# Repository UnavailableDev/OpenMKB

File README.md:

# OpenMKB
Modular keyboard (wip)

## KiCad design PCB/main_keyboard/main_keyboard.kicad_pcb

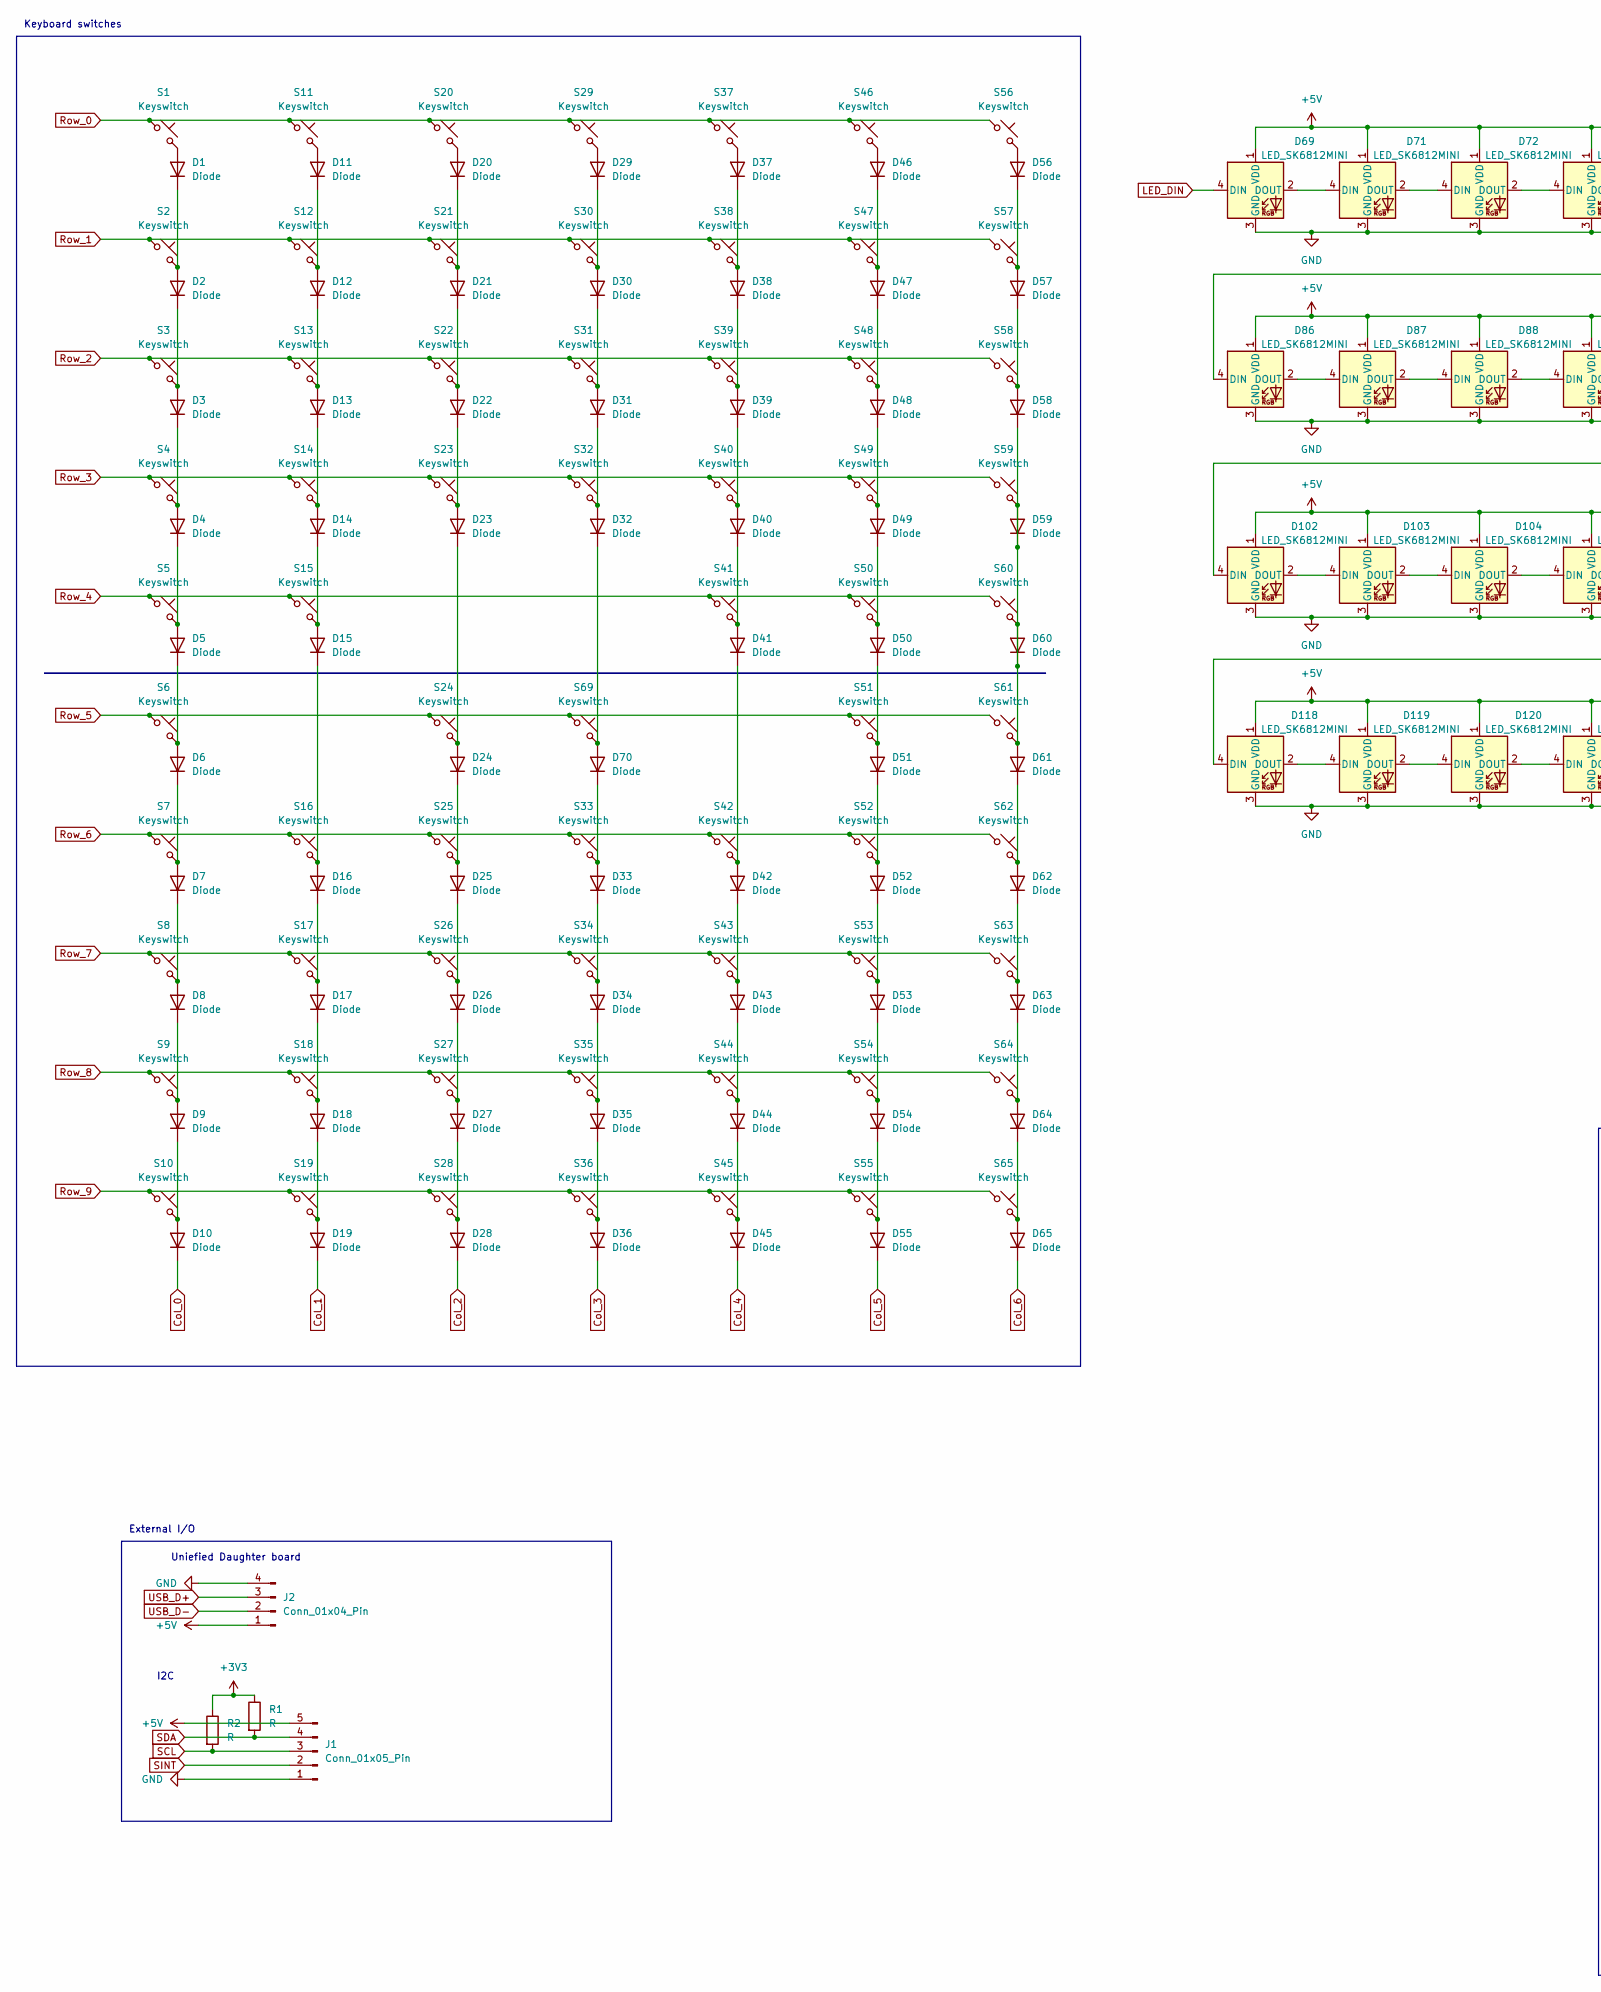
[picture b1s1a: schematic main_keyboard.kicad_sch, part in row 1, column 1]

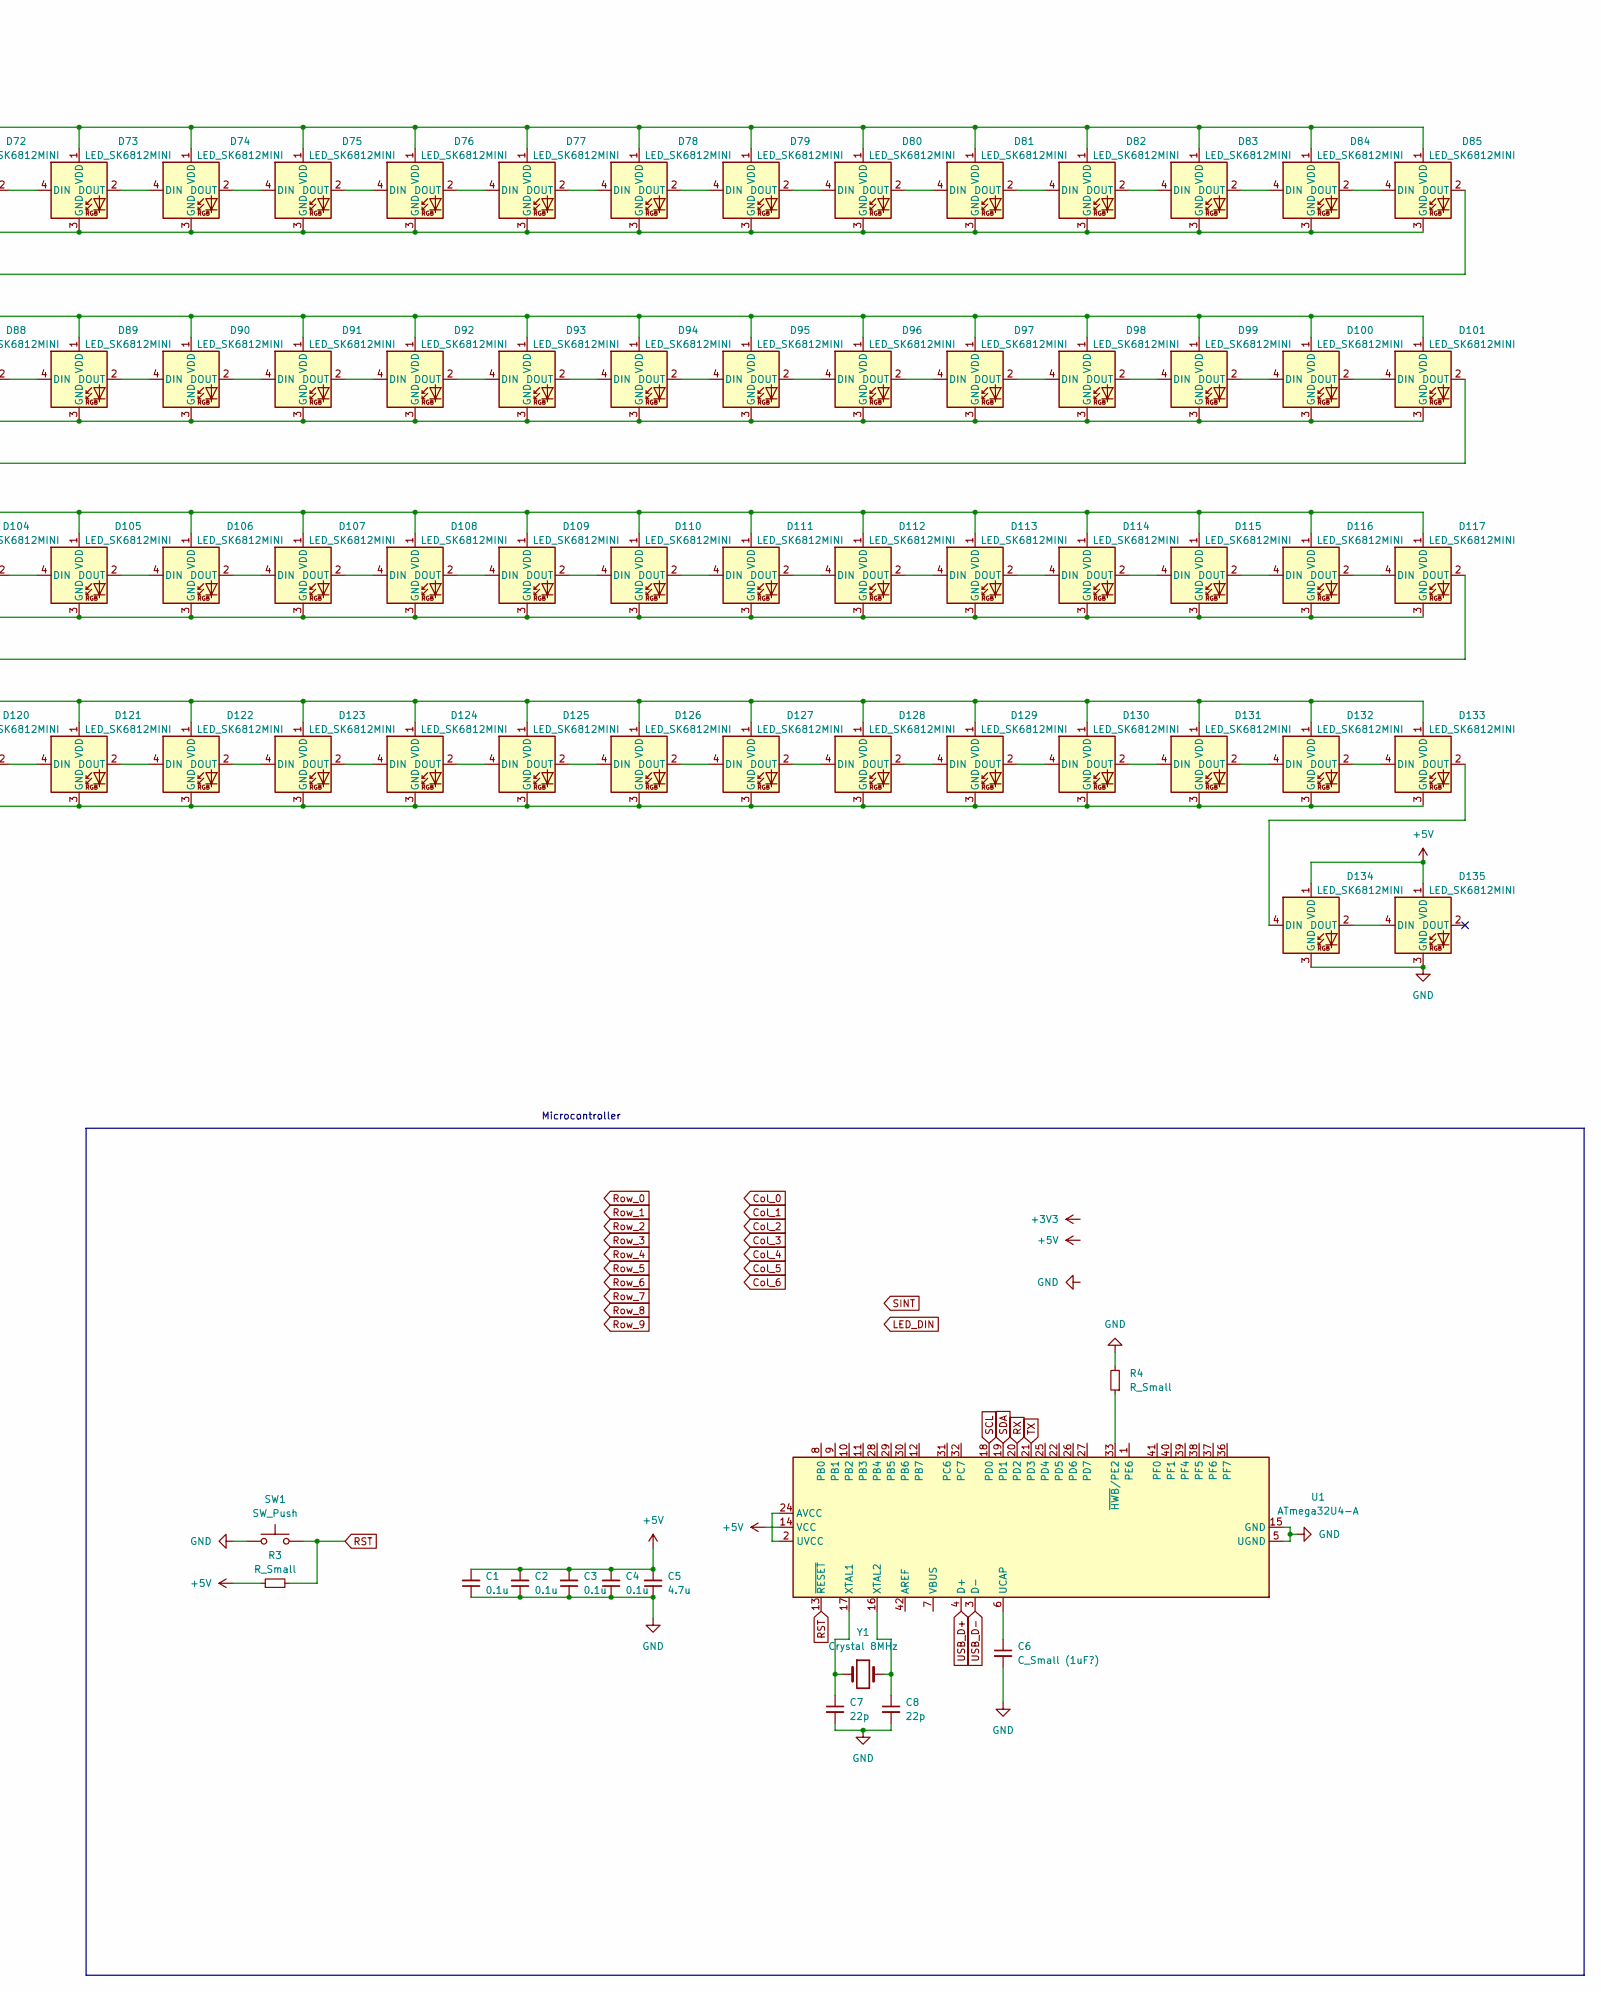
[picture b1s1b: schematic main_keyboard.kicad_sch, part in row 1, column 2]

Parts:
C1, C2, C3, C4: 0.1u; C_01005_0402Metric_Pad0.57x0.30mm_HandSolder
C5: 4.7u; C_0201_0603Metric_Pad0.64x0.40mm_HandSolder
C6: C_Small (1uF?)
C7, C8: 22p; C_01005_0402Metric_Pad0.57x0.30mm_HandSolder
D1, D2, D3, D4, D5, D6, D7, D8, D9, D10, D11, D12, D13, D14, D15, D16, D17, D18, D19, D20, D21, D22, D23, D24, D25, D26, D27, D28, D29, D30, D31, D32, D33, D34, D35, D36, D37, D38, D39, D40, D41, D42, D43, D44, D45, D46, D47, D48, D49, D50, D51, D52, D53, D54, D55, D56, D57, D58, D59, D60, D61, D62, D63, D64, D65, D70: Diode; Diode_SOD-123
D69, D71, D72, D73, D74, D75, D76, D77, D78, D79, D80, D81, D82, D83, D84, D85, D86, D87, D88, D89, D90, D91, D92, D93, D94, D95, D96, D97, D98, D99, D100, D101, D102, D103, D104, D105, D106, D107, D108, D109, D110, D111, D112, D113, D114, D115, D116, D117, D118, D119, D120, D121, D122, D123, D124, D125, D126, D127, D128, D129, D130, D131, D132, D133, D134, D135: LED_SK6812MINI
J1: Conn_01x05_Pin; FanPinHeader_1x03_P2.54mm_Vertical
J2: Conn_01x04_Pin
R1, R2: R
R3, R4: R_Small
S1, S7, S8, S9, S10, S11, S12, S13, S14, S16, S17, S18, S19, S20, S21, S22, S23, S25, S26, S27, S28, S29, S30, S31, S32, S33, S34, S35, S36, S37, S38, S39, S40, S42, S43, S44, S45, S46, S47, S48, S49, S51, S53, S54, S55, S56, S57, S59, S60, S61, S62, S63: Keyswitch; Hotswap_MX_Plated_1.00u
S2, S64: Keyswitch; Hotswap_MX_Plated_1.50u
S3, S24: Keyswitch; Hotswap_MX_Plated_1.75u
S4, S15, S58, S69: Keyswitch; Hotswap_MX_Plated_2.25u
S5, S6, S41, S50, S52: Keyswitch; Hotswap_MX_Plated_1.25u
S65: Keyswitch; Hotswap_MX_Plated_2.00u
SW1: SW_Push
U1: ATmega32U4-A; TQFP-44_10x10mm_P0.8mm
Y1: Crystal 8MHz

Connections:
+5V: C1.2, C2.2, C3.2, C4.2, C5.2, D69.1 (VDD), D71.1 (VDD), D72.1 (VDD), D73.1 (VDD), D74.1 (VDD), D75.1 (VDD), D76.1 (VDD), D77.1 (VDD), D78.1 (VDD), D79.1 (VDD), D80.1 (VDD), D81.1 (VDD), D82.1 (VDD), D83.1 (VDD), D84.1 (VDD), D85.1 (VDD), D86.1 (VDD), D87.1 (VDD), D88.1 (VDD), D89.1 (VDD), D90.1 (VDD), D91.1 (VDD), D92.1 (VDD), D93.1 (VDD), D94.1 (VDD), D95.1 (VDD), D96.1 (VDD), D97.1 (VDD), D98.1 (VDD), D99.1 (VDD), D100.1 (VDD), D101.1 (VDD), D102.1 (VDD), D103.1 (VDD), D104.1 (VDD), D105.1 (VDD), D106.1 (VDD), D107.1 (VDD), D108.1 (VDD), D109.1 (VDD), D110.1 (VDD), D111.1 (VDD), D112.1 (VDD), D113.1 (VDD), D114.1 (VDD), D115.1 (VDD), D116.1 (VDD), D117.1 (VDD), D118.1 (VDD), D119.1 (VDD), D120.1 (VDD), D121.1 (VDD), D122.1 (VDD), D123.1 (VDD), D124.1 (VDD), D125.1 (VDD), D126.1 (VDD), D127.1 (VDD), D128.1 (VDD), D129.1 (VDD), D130.1 (VDD), D131.1 (VDD), D132.1 (VDD), D133.1 (VDD), D134.1 (VDD), D135.1 (VDD), J1.5, J2.1, R3.1, U1.14 (VCC), U1.34 (VCC)
Col_0: D10.1 (K)
Col_1: D19.1 (K)
Col_2: D28.1 (K)
Col_3: D36.1 (K)
Col_4: D45.1 (K)
Col_5: D55.1 (K)
Col_6: D65.1 (K)
GND: C1.1, C2.1, C3.1, C4.1, C5.1, C6.2, C7.2, C8.2, D69.3 (GND), D71.3 (GND), D72.3 (GND), D73.3 (GND), D74.3 (GND), D75.3 (GND), D76.3 (GND), D77.3 (GND), D78.3 (GND), D79.3 (GND), D80.3 (GND), D81.3 (GND), D82.3 (GND), D83.3 (GND), D84.3 (GND), D85.3 (GND), D86.3 (GND), D87.3 (GND), D88.3 (GND), D89.3 (GND), D90.3 (GND), D91.3 (GND), D92.3 (GND), D93.3 (GND), D94.3 (GND), D95.3 (GND), D96.3 (GND), D97.3 (GND), D98.3 (GND), D99.3 (GND), D100.3 (GND), D101.3 (GND), D102.3 (GND), D103.3 (GND), D104.3 (GND), D105.3 (GND), D106.3 (GND), D107.3 (GND), D108.3 (GND), D109.3 (GND), D110.3 (GND), D111.3 (GND), D112.3 (GND), D113.3 (GND), D114.3 (GND), D115.3 (GND), D116.3 (GND), D117.3 (GND), D118.3 (GND), D119.3 (GND), D120.3 (GND), D121.3 (GND), D122.3 (GND), D123.3 (GND), D124.3 (GND), D125.3 (GND), D126.3 (GND), D127.3 (GND), D128.3 (GND), D129.3 (GND), D130.3 (GND), D131.3 (GND), D132.3 (GND), D133.3 (GND), D134.3 (GND), D135.3 (GND), J1.1, J2.4, R4.2, SW1.1, U1.5 (UGND), U1.15 (GND), U1.23 (GND), U1.35 (GND), U1.43 (GND)
LED_DIN: D69.4 (DIN)
unnamed: D1.2 (A), S1.2
unnamed: D1.1 (K), D2.2 (A), S2.2
unnamed: D2.1 (K), D3.2 (A), S3.2
unnamed: D3.1 (K), D4.2 (A), S4.2
unnamed: D4.1 (K), D5.2 (A), S5.2
unnamed: D5.1 (K), D6.2 (A), S6.2
unnamed: D6.1 (K), D7.2 (A), S7.2
unnamed: D7.1 (K), D8.2 (A), S8.2
unnamed: D8.1 (K), D9.2 (A), S9.2
unnamed: D9.1 (K), D10.2 (A), S10.2
unnamed: D11.2 (A), S11.2
unnamed: D11.1 (K), D12.2 (A), S12.2
unnamed: D12.1 (K), D13.2 (A), S13.2
unnamed: D13.1 (K), D14.2 (A), S14.2
unnamed: D14.1 (K), D15.2 (A), S15.2
unnamed: D15.1 (K), D16.2 (A), S16.2
unnamed: D16.1 (K), D17.2 (A), S17.2
unnamed: D17.1 (K), D18.2 (A), S18.2
unnamed: D18.1 (K), D19.2 (A), S19.2
unnamed: D20.2 (A), S20.2
unnamed: D20.1 (K), D21.2 (A), S21.2
unnamed: D21.1 (K), D22.2 (A), S22.2
unnamed: D22.1 (K), D23.2 (A), S23.2
unnamed: D23.1 (K), D24.2 (A), S24.2
unnamed: D24.1 (K), D25.2 (A), S25.2
unnamed: D25.1 (K), D26.2 (A), S26.2
unnamed: D26.1 (K), D27.2 (A), S27.2
unnamed: D27.1 (K), D28.2 (A), S28.2
unnamed: D29.2 (A), S29.2
unnamed: D29.1 (K), D30.2 (A), S30.2
unnamed: D30.1 (K), D31.2 (A), S31.2
unnamed: D31.1 (K), D32.2 (A), S32.2
unnamed: D32.1 (K), D70.2 (A), S69.2
unnamed: D33.2 (A), D70.1 (K), S33.2
unnamed: D33.1 (K), D34.2 (A), S34.2
unnamed: D34.1 (K), D35.2 (A), S35.2
unnamed: D35.1 (K), D36.2 (A), S36.2
unnamed: D37.2 (A), S37.2
unnamed: D37.1 (K), D38.2 (A), S38.2
unnamed: D38.1 (K), D39.2 (A), S39.2
unnamed: D39.1 (K), D40.2 (A), S40.2
unnamed: D40.1 (K), D41.2 (A), S41.2
unnamed: D41.1 (K), D42.2 (A), S42.2
unnamed: D42.1 (K), D43.2 (A), S43.2
unnamed: D43.1 (K), D44.2 (A), S44.2
unnamed: D44.1 (K), D45.2 (A), S45.2
unnamed: D46.2 (A), S46.2
unnamed: D46.1 (K), D47.2 (A), S47.2
unnamed: D47.1 (K), D48.2 (A), S48.2
unnamed: D48.1 (K), D49.2 (A), S49.2
unnamed: D49.1 (K), D50.2 (A), S50.2
unnamed: D50.1 (K), D51.2 (A), S51.2
unnamed: D51.1 (K), D52.2 (A), S52.2
unnamed: D52.1 (K), D53.2 (A), S53.2
unnamed: D53.1 (K), D54.2 (A), S54.2
unnamed: D54.1 (K), D55.2 (A), S55.2
unnamed: D56.2 (A), S56.2
unnamed: D56.1 (K), D57.2 (A), S57.2
unnamed: D57.1 (K), D58.2 (A), S58.2
unnamed: D58.1 (K), D59.1 (K), D59.2 (A), D60.1 (K), D60.2 (A), D61.2 (A), S59.2, S60.2, S61.2
unnamed: D61.1 (K), D62.2 (A), S62.2
unnamed: D62.1 (K), D63.2 (A), S63.2
unnamed: D63.1 (K), D64.2 (A), S64.2
unnamed: D64.1 (K), D65.2 (A), S65.2
unnamed: D69.2 (DOUT), D71.4 (DIN)
unnamed: D71.2 (DOUT), D72.4 (DIN)
unnamed: D72.2 (DOUT), D73.4 (DIN)
unnamed: D73.2 (DOUT), D74.4 (DIN)
unnamed: D74.2 (DOUT), D75.4 (DIN)
unnamed: D75.2 (DOUT), D76.4 (DIN)
unnamed: D76.2 (DOUT), D77.4 (DIN)
unnamed: D77.2 (DOUT), D78.4 (DIN)
unnamed: D78.2 (DOUT), D79.4 (DIN)
unnamed: D79.2 (DOUT), D80.4 (DIN)
unnamed: D80.2 (DOUT), D81.4 (DIN)
unnamed: D81.2 (DOUT), D82.4 (DIN)
unnamed: D82.2 (DOUT), D83.4 (DIN)
unnamed: D83.2 (DOUT), D84.4 (DIN)
unnamed: D84.2 (DOUT), D85.4 (DIN)
unnamed: D85.2 (DOUT), D86.4 (DIN)
unnamed: D86.2 (DOUT), D87.4 (DIN)
unnamed: D87.2 (DOUT), D88.4 (DIN)
unnamed: D88.2 (DOUT), D89.4 (DIN)
unnamed: D89.2 (DOUT), D90.4 (DIN)
unnamed: D90.2 (DOUT), D91.4 (DIN)
unnamed: D91.2 (DOUT), D92.4 (DIN)
unnamed: D92.2 (DOUT), D93.4 (DIN)
unnamed: D93.2 (DOUT), D94.4 (DIN)
unnamed: D94.2 (DOUT), D95.4 (DIN)
unnamed: D95.2 (DOUT), D96.4 (DIN)
unnamed: D96.2 (DOUT), D97.4 (DIN)
unnamed: D97.2 (DOUT), D98.4 (DIN)
unnamed: D98.2 (DOUT), D99.4 (DIN)
unnamed: D99.2 (DOUT), D100.4 (DIN)
unnamed: D100.2 (DOUT), D101.4 (DIN)
unnamed: D101.2 (DOUT), D102.4 (DIN)
unnamed: D102.2 (DOUT), D103.4 (DIN)
unnamed: D103.2 (DOUT), D104.4 (DIN)
unnamed: D104.2 (DOUT), D105.4 (DIN)
unnamed: D105.2 (DOUT), D106.4 (DIN)
unnamed: D106.2 (DOUT), D107.4 (DIN)
unnamed: D107.2 (DOUT), D108.4 (DIN)
unnamed: D108.2 (DOUT), D109.4 (DIN)
unnamed: D109.2 (DOUT), D110.4 (DIN)
unnamed: D110.2 (DOUT), D111.4 (DIN)
unnamed: D111.2 (DOUT), D112.4 (DIN)
unnamed: D112.2 (DOUT), D113.4 (DIN)
unnamed: D113.2 (DOUT), D114.4 (DIN)
unnamed: D114.2 (DOUT), D115.4 (DIN)
unnamed: D115.2 (DOUT), D116.4 (DIN)
unnamed: D116.2 (DOUT), D117.4 (DIN)
unnamed: D117.2 (DOUT), D118.4 (DIN)
unnamed: D118.2 (DOUT), D119.4 (DIN)
unnamed: D119.2 (DOUT), D120.4 (DIN)
unnamed: D120.2 (DOUT), D121.4 (DIN)
unnamed: D121.2 (DOUT), D122.4 (DIN)
unnamed: D122.2 (DOUT), D123.4 (DIN)
unnamed: D123.2 (DOUT), D124.4 (DIN)
unnamed: D124.2 (DOUT), D125.4 (DIN)
unnamed: D125.2 (DOUT), D126.4 (DIN)
unnamed: D126.2 (DOUT), D127.4 (DIN)
unnamed: D127.2 (DOUT), D128.4 (DIN)
unnamed: D128.2 (DOUT), D129.4 (DIN)
unnamed: D129.2 (DOUT), D130.4 (DIN)
unnamed: D130.2 (DOUT), D131.4 (DIN)
unnamed: D131.2 (DOUT), D132.4 (DIN)
unnamed: D132.2 (DOUT), D133.4 (DIN)
unnamed: D133.2 (DOUT), D134.4 (DIN)
unnamed: D134.2 (DOUT), D135.4 (DIN)
unnamed: R1.1, R2.1
unnamed: C6.1, U1.6 (UCAP)
unnamed: U1.2 (UVCC), U1.24 (AVCC), U1.44 (AVCC)
unnamed: C7.1, U1.17 (XTAL1), Y1.1
unnamed: C8.1, U1.16 (XTAL2), Y1.2
unnamed: R4.1, U1.33 (~HWB/PE2)
RST: R3.2, SW1.2, U1.13 (~RESET)
RX: U1.20 (PD2)
Row_0: S1.1, S11.1, S20.1, S29.1, S37.1, S46.1, S56.1
Row_1: S2.1, S12.1, S21.1, S30.1, S38.1, S47.1, S57.1
Row_2: S3.1, S13.1, S22.1, S31.1, S39.1, S48.1, S58.1
Row_3: S4.1, S14.1, S23.1, S32.1, S40.1, S49.1, S59.1
Row_4: S5.1, S15.1, S41.1, S50.1, S60.1
Row_5: S6.1, S24.1, S51.1, S61.1, S69.1
Row_6: S7.1, S16.1, S25.1, S33.1, S42.1, S52.1, S62.1
Row_7: S8.1, S17.1, S26.1, S34.1, S43.1, S53.1, S63.1
Row_8: S9.1, S18.1, S27.1, S35.1, S44.1, S54.1, S64.1
Row_9: S10.1, S19.1, S28.1, S36.1, S45.1, S55.1, S65.1
SCL: J1.3, R2.2, U1.18 (PD0)
SDA: J1.4, R1.2, U1.19 (PD1)
SINT: J1.2
TX: U1.21 (PD3)
USB_D+: J2.3, U1.4 (D+)
USB_D-: J2.2, U1.3 (D-)

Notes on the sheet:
External I/O
I2C
Keyboard switches
Uniefied Daughter board
Microcontroller

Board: 2 copper layers, 213 parts (68 on the bottom side), 145 nets, no tracks yet.

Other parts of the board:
Stab1, Stab3, Stab3#2: Stabilizer_MX_2.00u
Stab 2u, Stab 2u#2: Stabilizer_MX_2.00u
Stab 6u: Stabilizer_MX_6.25u

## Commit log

2024-01-24 KiCAD mod_1x5 (eod)
2024-01-24 Init KiCAD main_board
2024-01-25 added main_board layout
2024-01-25 Generic switch matrix created
2024-01-26 Added plate #7 layout
2024-01-26 Added virtual rows to key matrix #6
    The "vritual" rows reduce GPIO usage with matrix from (5+16=21) to (10+8=18)
2024-02-01 Layout partial completion
2024-02-25 leds placed
    smd led footprints placed
2024-03-02 First draft Main board
2024-03-03 GND plane fix
    Ensured proper connection between all ground planes
2024-03-20 corne keymap v0.1
2024-03-20 added qwerty alternative v0.1
2024-03-20 swapped LALT and LGUI positions
2024-03-22 changed layer switching
